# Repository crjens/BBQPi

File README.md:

BBQPi
=====

Raspberry Pi BBQ meter

Install Instructions
--------------------

1. Start with latest Raspian image from http://downloads.raspberrypi.org/raspbian_latest
2. login to Pi with Putty or other 
3. run 'sudo raspi-config' 
	1. set locale and timezone under internationalisation options
	2. enable SPI and I2C under Advanced Options
	3. expand filesystem
4. Enable I2C by adding the following two lines to /etc/modules
	1. i2c-bcm2708 
	2. i2c-dev
5. Install nodejs:
	1.	wget http://nodejs.org/dist/v0.10.28/node-v0.10.28-linux-arm-pi.tar.gz
	2.	tar -xvzf node-v0.10.28-linux-arm-pi.tar.gz
	3.  create symbolic links to node and npm
		1.	sudo ln -s /home/pi/node-v0.10.28-linux-arm-pi/bin/node /usr/bin/node
		2.	sudo ln -s /home/pi/node-v0.10.28-linux-arm-pi/bin/npm /usr/bin/npm
	4. (both node -v and npm -v should now show current version)
6. Clone BBQPi into app directory
	1. git clone https://github.com/crjens/BBQPi.git app
7. cd into the 'app' directory and type 'npm install'

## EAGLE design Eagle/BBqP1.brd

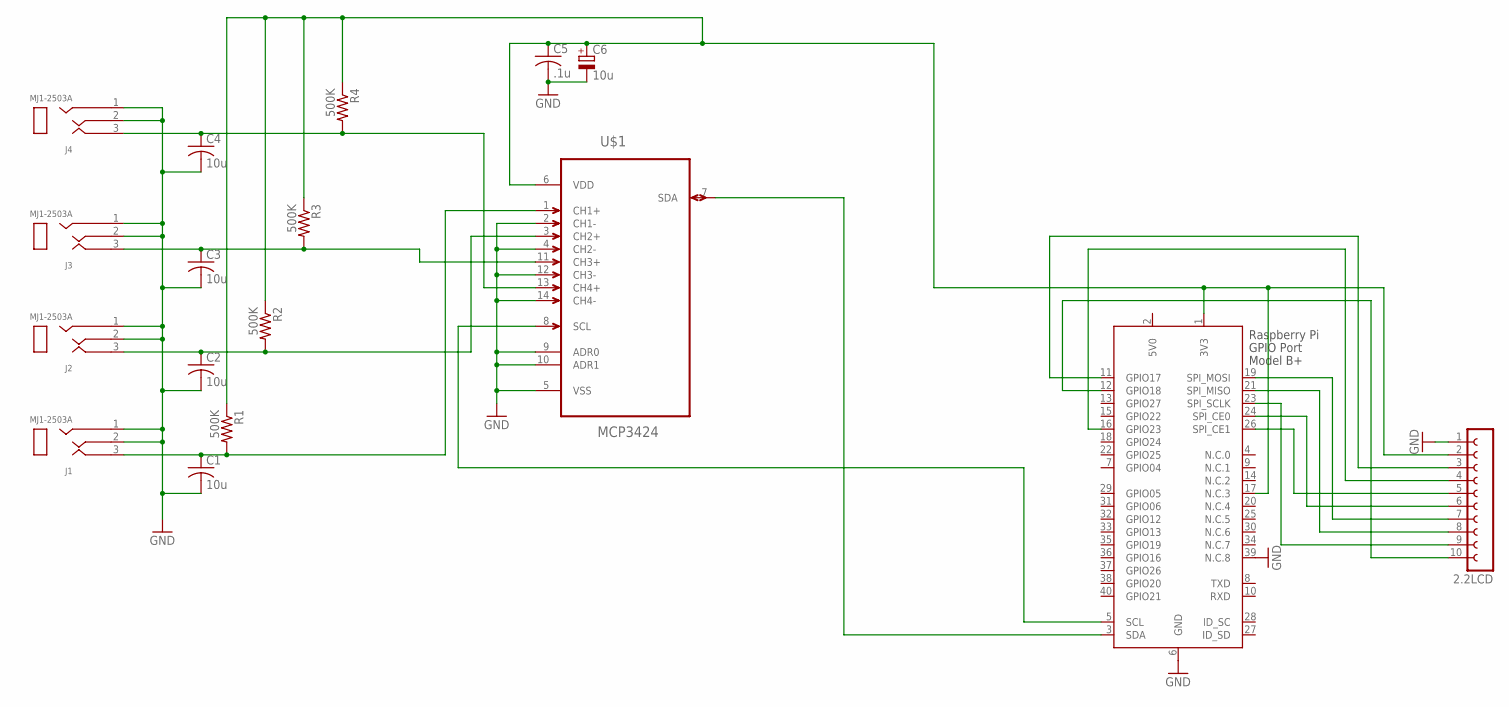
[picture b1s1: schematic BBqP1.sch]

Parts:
2.2LCD: FE10-1; FE10
C1, C2, C3, C4: 10u; C1206; MPN C1206C106M4RACTU
C5: .1u; C1206; MPN C1206C104K5RACAUTO
C6: 10u; SMC_C; MPN T491C106M016AT
J1, J2, J3, J4: MJ1-2503A
R1, R2, R3, R4: 500K; R1206; MPN CRCW1206510KFKEA
U$1: MCP3424; SOIC127P600X175-14N
X1: RASPI_BOARD_B+_H; RASPI_BOARD_B+HAT

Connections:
3V3: 2.2LCD.2, C5.1, C6.+, R1.1, R2.1, R3.1, R4.1, U$1.6 (VDD), X1.1 (3V3), X1.17 (N.C.3)
5V0: X1.2 (5V0)
GND: 2.2LCD.1, C1.2, C2.2, C3.2, C4.2, C5.2, C6.-, J1.1, J1.2, J2.1, J2.2, J3.1, J3.2, J4.1, J4.2, U$1.2 (CH1-), U$1.4 (CH2-), U$1.5 (VSS), U$1.9 (ADR0), U$1.10 (ADR1), U$1.12 (CH3-), U$1.14 (CH4-), X1.6 (GND), X1.39 (N.C.8)
unnamed: C4.1, J4.3, R4.2, U$1.13 (CH4+)
unnamed: 2.2LCD.10, X1.12 (GPIO18)
unnamed: C3.1, J3.3, R3.2, U$1.11 (CH3+)
unnamed: C2.1, J2.3, R2.2, U$1.3 (CH2+)
unnamed: C1.1, J1.3, R1.2, U$1.1 (CH1+)
unnamed: 2.2LCD.4, X1.16 (GPIO23)
unnamed: 2.2LCD.8, X1.21 (SPI_MISO)
unnamed: U$1.8 (SCL), X1.5 (SCL)
unnamed: 2.2LCD.7, X1.19 (SPI_MOSI)
unnamed: 2.2LCD.6, X1.24 (SPI_CE0)
unnamed: U$1.7 (SDA), X1.3 (SDA)
unnamed: 2.2LCD.5, X1.26 (SPI_CE1)
unnamed: 2.2LCD.9, X1.23 (SPI_SCLK)
unnamed: 2.2LCD.3, X1.11 (GPIO17)

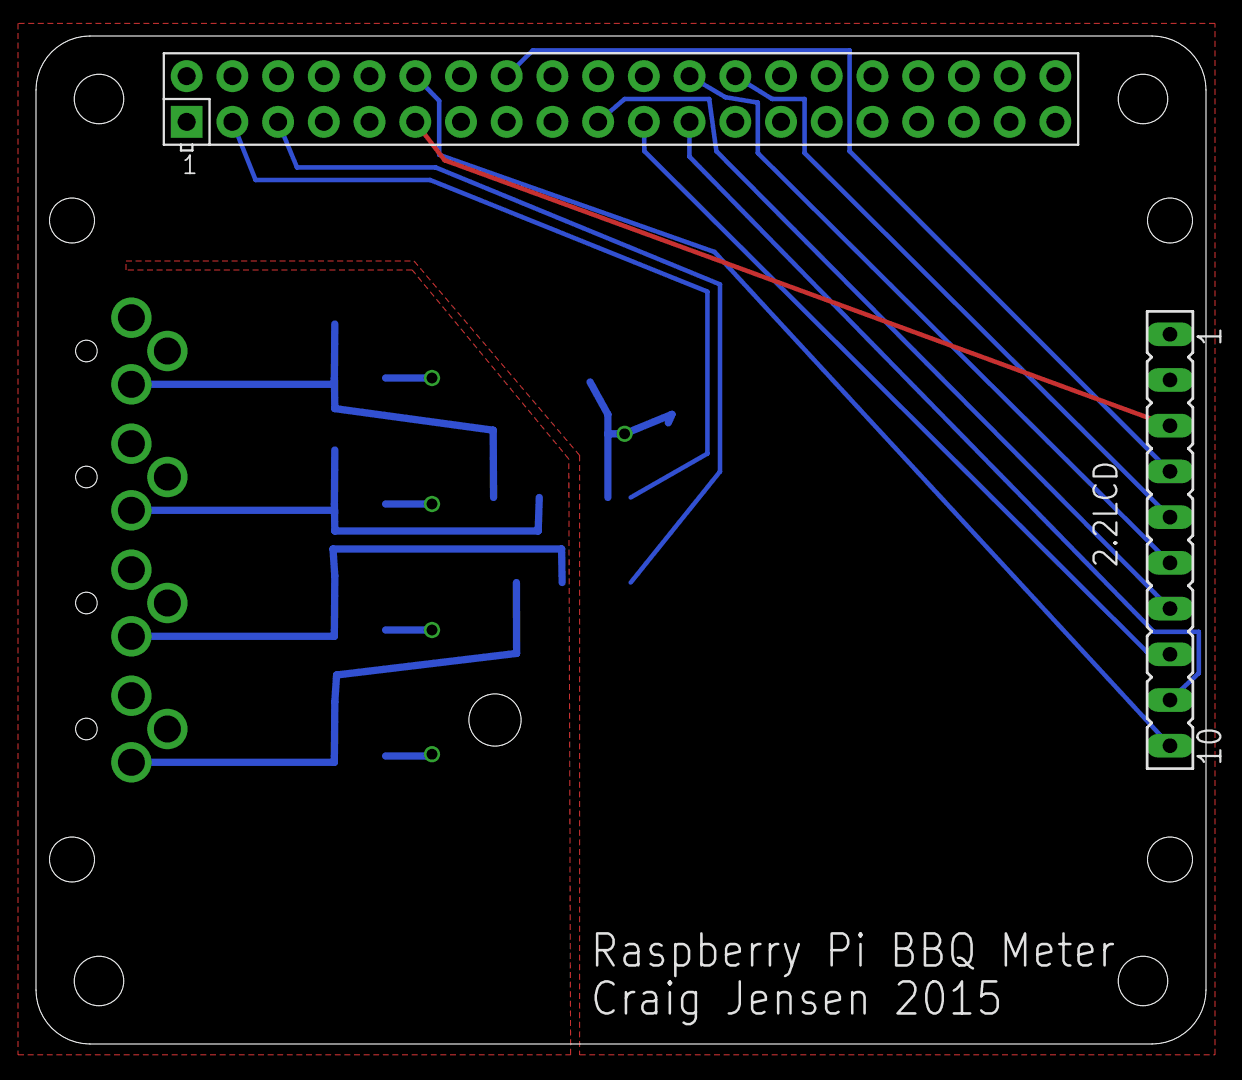
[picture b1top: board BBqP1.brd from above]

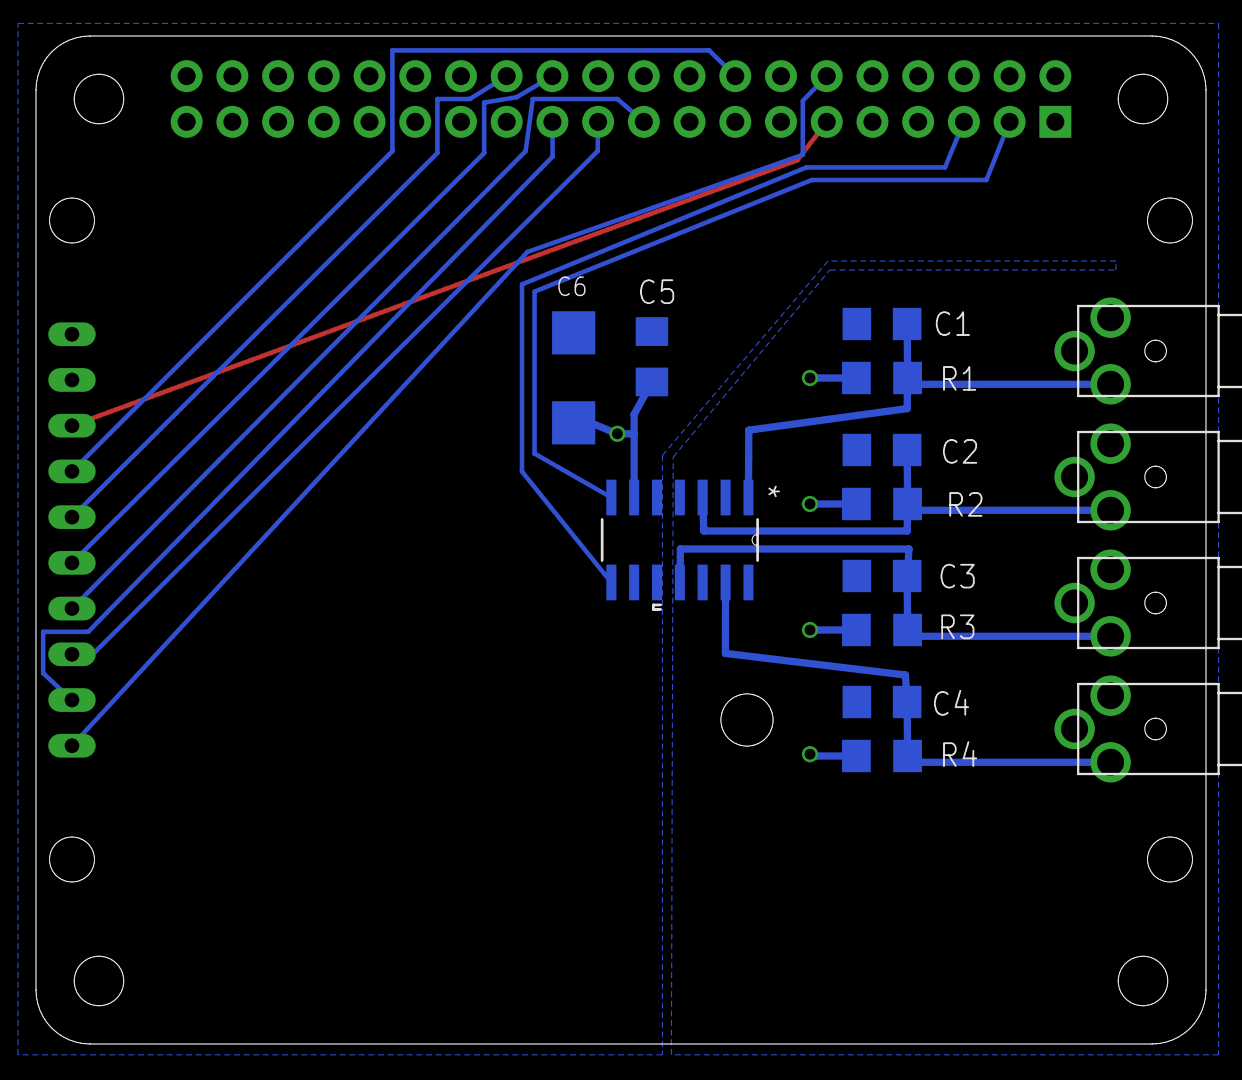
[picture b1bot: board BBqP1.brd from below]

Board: 2 copper layers, 65.0 x 56.0 mm, 17 parts (15 on the bottom side), 16 nets.

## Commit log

2015-01-05 Add Eagle files
2015-01-06 Added display files
2015-01-07 Updated display code
2015-01-07 Add package files
2015-01-07 Updated install scripts
2015-01-07 Fix line breaks
2015-01-07 Adding 3d files
    This set is pre-board measurements, they are close, but may be slightly
    off. Final adjustments will not be fun.
2015-01-07 Show ip address on startup
2015-01-08 Add BBQ functionality
2015-01-08 fixed i2c version
2015-01-08 Updated install and fixed database initialization
2015-01-08 Bug fixes and cleanup
2015-01-09 changed to unix line breaks
2015-01-13 Merging in the smartthings request code
    Smartthings integration. useful only if you have smartthings.
2015-03-06 updated with new install procedure
2015-03-09 updated readme and i2c version
2015-03-09 revert version of i2c
2015-03-09 rerevert i2c version
2015-03-09 update install script

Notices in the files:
parts and their libraries:
con-cuistack: Copyright (C) 2008, Bob Starr
